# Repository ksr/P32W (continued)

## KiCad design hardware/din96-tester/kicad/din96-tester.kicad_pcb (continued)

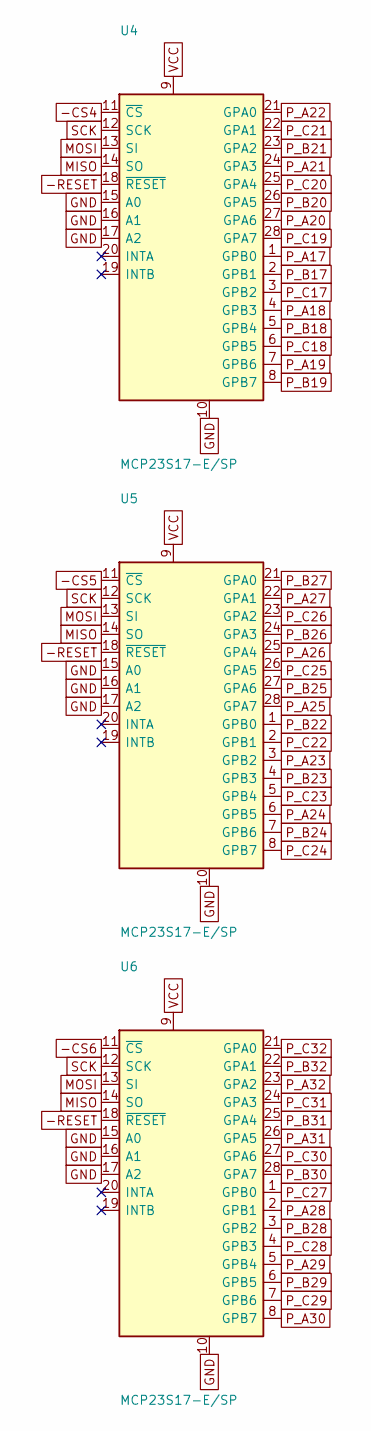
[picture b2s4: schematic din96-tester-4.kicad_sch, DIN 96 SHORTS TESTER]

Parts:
U4, U5, U6: MCP23S17-E/SP; DIP-28_W7.62mm

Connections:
-CS4: U4.11 (~CS); also elsewhere on the board
-CS5: U5.11 (~CS); also elsewhere on the board
-CS6: U6.11 (~CS); also elsewhere on the board
-RESET: U4.18 (~RESET), U5.18 (~RESET), U6.18 (~RESET); also elsewhere on the board
GND: U4.10, U4.15 (A0), U4.16 (A1), U4.17 (A2), U5.10, U5.15 (A0), U5.16 (A1), U5.17 (A2), U6.10, U6.15 (A0), U6.16 (A1), U6.17 (A2); also elsewhere on the board
MISO: U4.14 (SO), U5.14 (SO), U6.14 (SO); also elsewhere on the board
MOSI: U4.13 (SI), U5.13 (SI), U6.13 (SI); also elsewhere on the board
P_A17: U4.1 (GPB0); also elsewhere on the board
P_A18: U4.4 (GPB3); also elsewhere on the board
P_A19: U4.7 (GPB6); also elsewhere on the board
P_A20: U4.27 (GPA6); also elsewhere on the board
P_A21: U4.24 (GPA3); also elsewhere on the board
P_A22: U4.21 (GPA0); also elsewhere on the board
P_A23: U5.3 (GPB2); also elsewhere on the board
P_A24: U5.6 (GPB5); also elsewhere on the board
P_A25: U5.28 (GPA7); also elsewhere on the board
P_A26: U5.25 (GPA4); also elsewhere on the board
P_A27: U5.22 (GPA1); also elsewhere on the board
P_A28: U6.2 (GPB1); also elsewhere on the board
P_A29: U6.5 (GPB4); also elsewhere on the board
P_A30: U6.8 (GPB7); also elsewhere on the board
P_A31: U6.26 (GPA5); also elsewhere on the board
P_A32: U6.23 (GPA2); also elsewhere on the board
P_B17: U4.2 (GPB1); also elsewhere on the board
P_B18: U4.5 (GPB4); also elsewhere on the board
P_B19: U4.8 (GPB7); also elsewhere on the board
P_B20: U4.26 (GPA5); also elsewhere on the board
P_B21: U4.23 (GPA2); also elsewhere on the board
P_B22: U5.1 (GPB0); also elsewhere on the board
P_B23: U5.4 (GPB3); also elsewhere on the board
P_B24: U5.7 (GPB6); also elsewhere on the board
P_B25: U5.27 (GPA6); also elsewhere on the board
P_B26: U5.24 (GPA3); also elsewhere on the board
P_B27: U5.21 (GPA0); also elsewhere on the board
P_B28: U6.3 (GPB2); also elsewhere on the board
P_B29: U6.6 (GPB5); also elsewhere on the board
P_B30: U6.28 (GPA7); also elsewhere on the board
P_B31: U6.25 (GPA4); also elsewhere on the board
P_B32: U6.22 (GPA1); also elsewhere on the board
P_C17: U4.3 (GPB2); also elsewhere on the board
P_C18: U4.6 (GPB5); also elsewhere on the board
P_C19: U4.28 (GPA7); also elsewhere on the board
P_C20: U4.25 (GPA4); also elsewhere on the board
P_C21: U4.22 (GPA1); also elsewhere on the board
P_C22: U5.2 (GPB1); also elsewhere on the board
P_C23: U5.5 (GPB4); also elsewhere on the board
P_C24: U5.8 (GPB7); also elsewhere on the board
P_C25: U5.26 (GPA5); also elsewhere on the board
P_C26: U5.23 (GPA2); also elsewhere on the board
P_C27: U6.1 (GPB0); also elsewhere on the board
P_C28: U6.4 (GPB3); also elsewhere on the board
P_C29: U6.7 (GPB6); also elsewhere on the board
P_C30: U6.27 (GPA6); also elsewhere on the board
P_C31: U6.24 (GPA3); also elsewhere on the board
P_C32: U6.21 (GPA0); also elsewhere on the board
SCK: U4.12 (SCK), U5.12 (SCK), U6.12 (SCK); also elsewhere on the board
VCC: U4.9, U5.9, U6.9; also elsewhere on the board

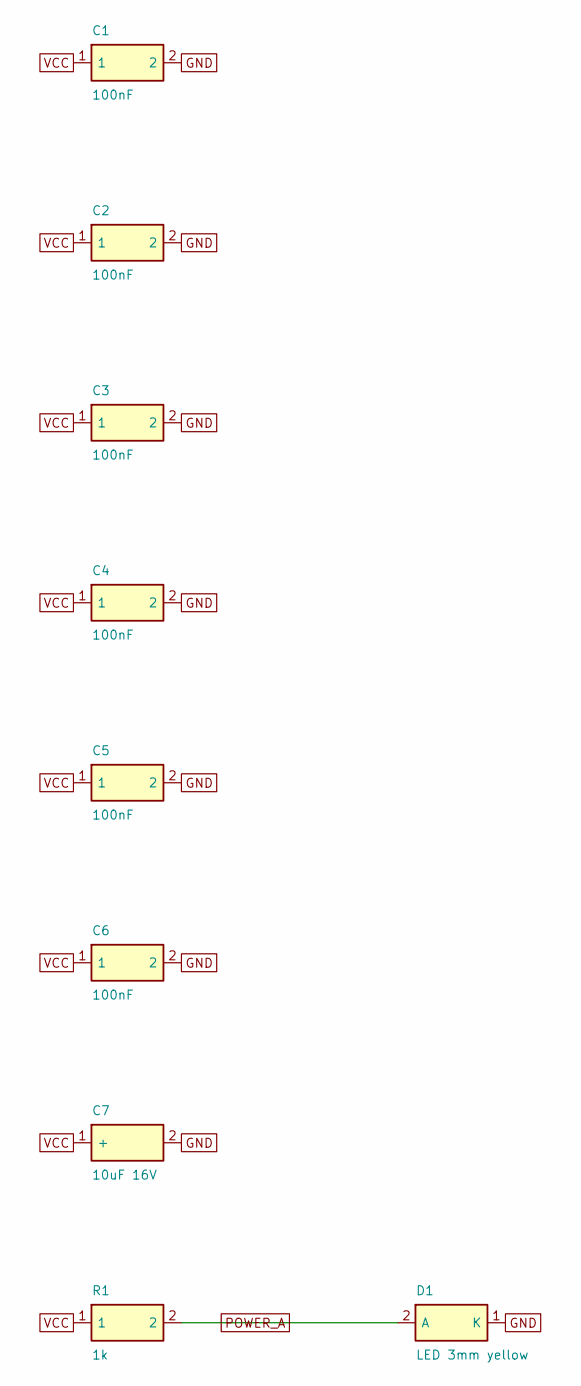
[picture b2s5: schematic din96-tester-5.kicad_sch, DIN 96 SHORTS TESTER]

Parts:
C1, C2, C3, C4, C5, C6: 100nF; C_Disc_D3.0mm_W2.0mm_P2.50mm
C7: 10uF 16V; CP_Radial_D5.0mm_P2.00mm
D1: LED 3mm yellow; LED_D3.0mm
R1: 1k; R_Axial_DIN0207_L6.3mm_D2.5mm_P10.16mm_Horizontal

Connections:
GND: C1.2, C2.2, C3.2, C4.2, C5.2, C6.2, C7.2 (~), D1.1 (K); also elsewhere on the board
POWER_A: D1.2 (A), R1.2
VCC: C1.1, C2.1, C3.1, C4.1, C5.1, C6.1, C7.1 (+), R1.1; also elsewhere on the board

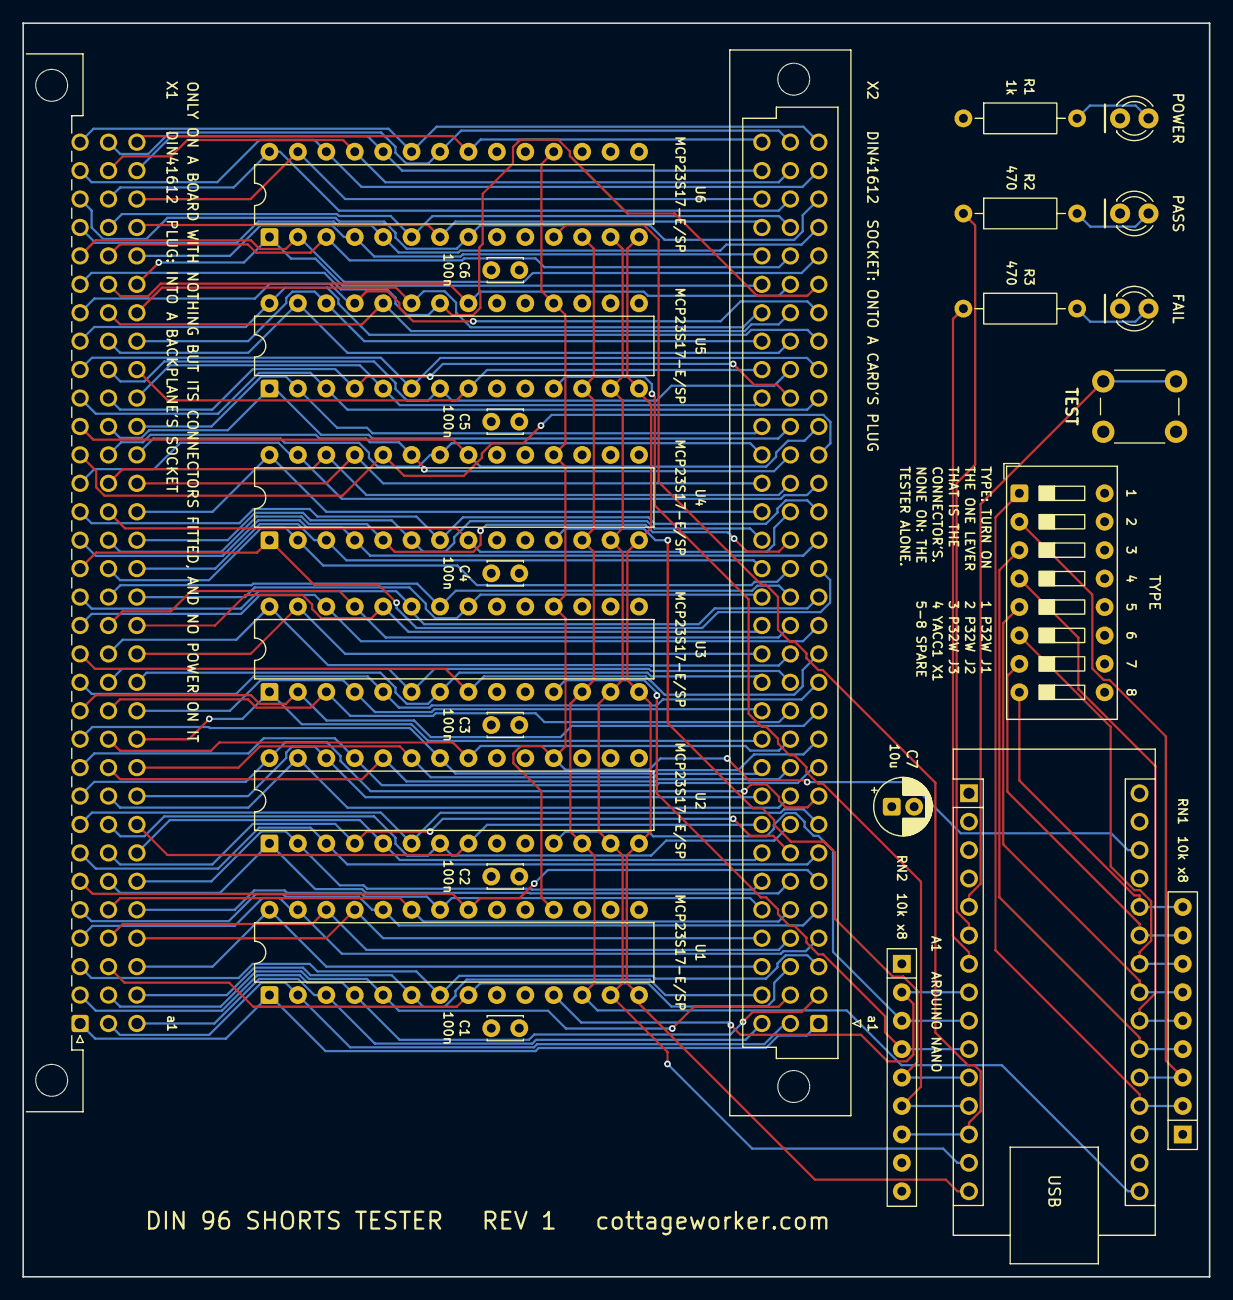
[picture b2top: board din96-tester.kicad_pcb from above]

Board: 4 copper layers, 106.0 x 112.0 mm, 26 parts (0 on the bottom side), 122 nets.
